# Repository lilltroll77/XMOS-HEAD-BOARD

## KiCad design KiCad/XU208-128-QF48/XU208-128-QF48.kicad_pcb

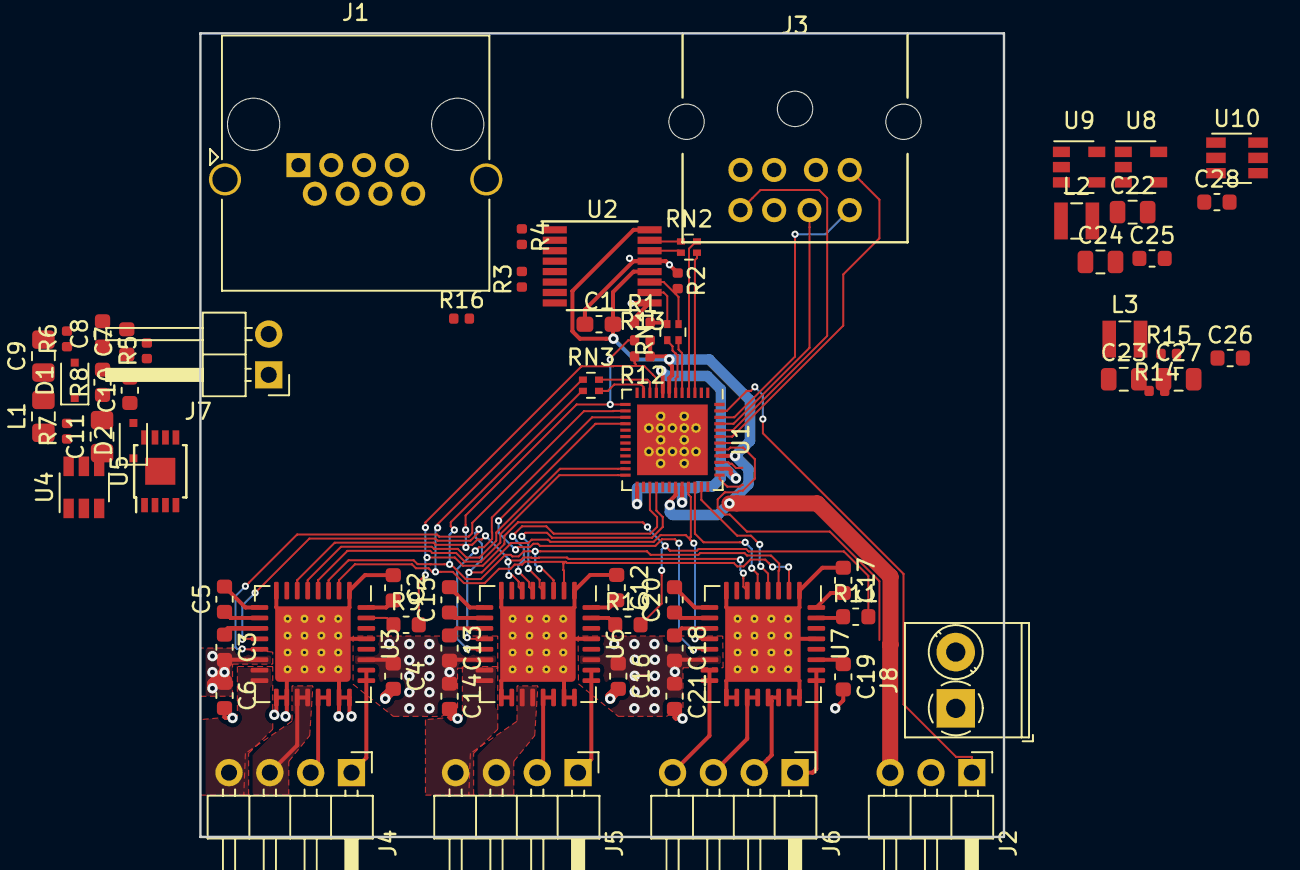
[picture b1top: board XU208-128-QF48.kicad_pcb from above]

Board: 2 copper layers, 50.0 x 50.0 mm, 70 parts (0 on the bottom side), 86 nets.

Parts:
C1: 100nF; C_0603_1608Metric_Pad1.05x0.95mm_HandSolder
C2, C4, C5, C6, C12, C14, C15, C16, C17, C19, C20, C21: 100nF; C_0603_1608Metric
C3, C13, C18: 220nF; C_0603_1608Metric
C7, C8: 1nF; C_0603_1608Metric
C9, C11: 4u7; C_0805_2012Metric_Pad1.15x1.40mm_HandSolder
C10: 1uF; C_0603_1608Metric
C22, C27: 22uF; C_0805_2012Metric
C23, C24: 2u2F; C_0805_2012Metric
C25, C26: 100n; C_0603_1608Metric
C28: 470p; C_0603_1608Metric
D1, D2: SCHOTTKY_DIODE; D_SOD-323F
J1: RJ45_Shielded; RJ45_Amphenol_RJHSE5380
J2: ZLIM; PinHeader_1x03_P2.54mm_Horizontal
J3: Mini-DIN-8; MDC-278
J4, J5, J6: Conn_01x04; PinHeader_1x04_P2.54mm_Horizontal
J7: LED; PinHeader_1x02_P2.54mm_Horizontal
J8: Screw_Terminal_01x02; TerminalBlock_Phoenix_PT-1,5-2-3.5-H_1x02_P3.50mm_Horizontal
L1: 22uH; C_0805_2012Metric_Pad1.15x1.40mm_HandSolder
L2, L3: 4u7; L_Wuerth_MAPI-2510
R1, R2, R7: 47k; R_0402_1005Metric
R3, R4: 100R; R_0402_1005Metric
R5, R6: 33k; R_0402_1005Metric
R8: 1R; R_0603_1608Metric
R9, R10, R11: 33R; R_0603_1608Metric
R12, R13: 3k3; R_0402_1005Metric
R14: 15k; R_0402_1005Metric
R15, R16: 10k; R_0402_1005Metric
RN1, RN2, RN3: 33R; R_Array_Convex_2x0402
U1: XU208-128-QF48-I10; QFN-48-1EP_6x6mm_P0.4mm_EP4.66x4.66mm_ThermalVias
U2: DS90LV049TMT; TSSOP-16_4.4x5mm_P0.65mm
U3, U6, U7: AMIS-30543; QFN-32-1EP_7x7mm_P0.65mm_EP4.7x4.7mm_ThermalVias
U4, U10: NCP308SN090T1G; TSOT-23-6
U5: LM3407MY; MSOP-8-1EP_3x3mm_P0.65mm_EP1.68x1.88mm
U8: TPS560430X3FDBVT; SOT-23-5
U9: TPS560430XFDBVR; SOT-23-5

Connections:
+1V0: C27.2, L3.2, U1.8, U1.25, U1.32, U1.38, U9.3, U10.5
+3V3: C1.2, C22.2, J2.3, L2.2, R12.1, R13.2, R14.1, R16.1, U1.7, U1.31, U1.40, U2.12, U2.16, U4.6, U8.3, U10.6
+24V: C3.2, C4.1, C6.1, C9.1, C11.2, C13.2, C14.1, C16.1, C18.2, C19.1, C21.1, C23.2, C24.2, D2.2, J7.2, J8.1, U3.14, U3.27, U5.5, U6.14, U6.27, U7.14, U7.27, U8.4, U8.5, U9.5
/1A: RN3.3, U1.11
/1B: R9.2, R10.2, R11.2, R12.2, U1.9
/1C: RN3.4, U1.10
/1D: R13.1, U1.13, U3.6, U6.6, U7.6
/1L: U1.33, U3.12, U6.12, U7.12
/1N: J2.1, U1.47
/4B1: U1.14, U3.13
/4B2: U1.15, U6.13
/4B3: U1.16, U7.13
/4C0: U1.23, U3.5
/4C1: U1.24, U3.4
/4D0: U1.27, U6.5
/4D1: U1.28, U6.4
/4E0: U1.34, U7.5
/4E1: U1.35, U7.4
/4F0: C7.2, U1.36
/4F1: U1.37, U5.2
/AMIS30543A/5V_VDD: C2.2, U3.32
/AMIS30543A/CPN: C5.2, U3.9
/AMIS30543A/DO: R9.1, U3.31
/AMIS30543A/XN: J4.2, U3.21, U3.22
/AMIS30543A/XP: J4.1, U3.25, U3.26
/AMIS30543A/YN: J4.4, U3.15, U3.16
/AMIS30543A/YP: J4.3, U3.19, U3.20
/AMIS30543B/5V_VDD: C12.2, U6.32
/AMIS30543B/CPN: C15.2, U6.9
/AMIS30543B/DO: R10.1, U6.31
/AMIS30543B/XN: J5.2, U6.21, U6.22
/AMIS30543B/XP: J5.1, U6.25, U6.26
/AMIS30543B/YN: J5.4, U6.15, U6.16
/AMIS30543B/YP: J5.3, U6.19, U6.20
/AMIS30543C/5V_VDD: C17.2, U7.32
/AMIS30543C/CPN: C20.2, U7.9
/AMIS30543C/DO: R11.1, U7.31
/AMIS30543C/XN: J6.2, U7.21, U7.22
/AMIS30543C/XP: J6.1, U7.25, U7.26
/AMIS30543C/YN: J6.4, U7.15, U7.16
/AMIS30543C/YP: J6.3, U7.19, U7.20
/CLK: RN3.2, U3.3, U6.3, U7.3
/FS: R7.1, U5.4
/JTAG/~TRST: J3.2, U10.3
/L0.in0: RN2.4, U1.4
/L0.in1: RN2.3, U1.3
/L0.out0: RN1.2, U1.5
/L0.out1: RN1.1, U1.6
/LED-: C11.1, J7.1, L1.1
/LED_EN: U4.1, U5.3
/LVDS.in0: R2.2, RN1.3, U2.11
/LVDS.in1: R1.2, RN1.4, U2.10
/LVDS.out0: RN2.1, U2.15
/LVDS.out1: RN2.2, U2.14
/LVDS/L.in0+: J1.3, R4.2, U2.2
/LVDS/L.in0-: J1.6, R4.1, U2.1
/LVDS/L.in1+: J1.7, R3.2, U2.3
/LVDS/L.in1-: J1.8, R3.1, U2.4
/LVDS/L.out0+: J1.1, U2.6
/LVDS/L.out0-: J1.2, U2.5
/LVDS/L.out1+: J1.4, U2.7
/LVDS/L.out1-: J1.5, U2.8
/LX: D2.1, L1.2, U5.8
/MOSI: RN3.1, U3.2, U6.2, U7.2
/PG3V3: R14.2, R15.1, U9.4
/TCK: J3.6, U1.44
/TDI: J3.7, U1.45
/TDO: J3.8, U1.46
/TMS: J3.5, U1.43
/~RST: R16.2, U1.41, U4.3, U10.1
GND: C1.1, C2.1, C4.2, C6.2, C8.1, C9.2, C10.1, C12.1, C14.2, C16.2, C17.1, C19.2, C21.2, C22.1, C23.1, C24.1, C27.1, C28.1, J1.SH, J2.2, J3.1, J3.4, J8.2, R1.1, R2.1, R5.2, R6.2, R7.2, R8.2, R15.2, U1.49, U2.9, U2.13, U3.1, U3.8, U3.17, U3.18, U3.23, U3.24, U3.29, U3.33, U4.2, U5.7, U5.9, U6.1, U6.8, U6.17, U6.18, U6.23, U6.24, U6.29, U6.33, U7.1, U7.8, U7.17, U7.18, U7.23, U7.24, U7.29, U7.33, U8.2, U9.2, U10.2
unnamed: C3.1, U3.11
unnamed: C5.1, U3.10
unnamed: C7.1, D1.1, R5.1
unnamed: C8.2, D1.2, R6.1, U4.5
unnamed: C10.2, U5.6
unnamed: C13.1, U6.11
unnamed: C15.1, U6.10
unnamed: C18.1, U7.11
unnamed: C20.1, U7.10
unnamed: C25.1, L2.1
unnamed: C25.2, U8.1
unnamed: C26.1, L3.1
unnamed: C26.2, U9.1
unnamed: C28.2, U10.4
unnamed: R8.1, U5.1

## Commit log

2019-01-09 added lib
2019-01-09 Added KiCad files
2019-01-10 Schematic and board
